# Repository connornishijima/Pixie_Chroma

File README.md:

<br>

**PIXIE CHROMA** is a dual-5x7 character display for Arduino, that can be easily chained to create easy-to-use displays as long or tall as you'd like! Featuring 70 addressable RGB LEDs, Pixie Chroma can be controlled with as little as a single GPIO! (***Make sure to [follow our Twitter](https://twitter.com/lixielabs) for official news!***)

---------------------------------------------------------------------------------
<p align="center">
  &nbsp;&nbsp;· · ·&nbsp;&nbsp;
  <a href="https://connornishijima.github.io/Pixie_Chroma/?section=getting-started"><b>GETTING STARTED</b></a>
  &nbsp;&nbsp;· · ·&nbsp;&nbsp;
  <a href="https://connornishijima.github.io/Pixie_Chroma/?section=docs"><b>LIBRARY DOCS</b></a>
  &nbsp;&nbsp;· · ·&nbsp;&nbsp;
  <a href="https://connornishijima.github.io/Pixie_Chroma/?section=datasheet"><b>DATASHEET</b></a>
  &nbsp;&nbsp;· · ·&nbsp;&nbsp;
  <a href="https://github.com/connornishijima/Pixie_Chroma/tree/main/extras/OSHW"><b>OSHW</b></a>
  &nbsp;&nbsp;· · ·&nbsp;&nbsp;
  <a href="https://connornishijima.github.io/Pixie_Chroma/?section=purchase"><b>PURCHASE</b></a>
  &nbsp;&nbsp;· · ·&nbsp;&nbsp;
</p>
<p align="center">

</p>

---------------------------------------------------------------------------------

# Pixie Chroma Is the Display We Always Wanted

**Pixie Chroma is a project that we here at Lixie Labs are incredibly passionate about!** In this third iteration, we have finally created the best RGB text display we've ever used. While we loved our original Pixie models, we felt that you couldn't get the same level of creativity that you **can** get with Pixie Chroma. With its ability to be dropped into any breadboard and coded with any experience level, these displays have a wide range of potential uses, meaning anybody in the maker community can find a use for them! Pixie Chroma is our gift to you.

# Two Big New Features

Along with full RGB control, and an absolute **UNIT** of an Arduino Library, we are introducing two other **big** new features with this release: **Quad Mode** and **Shortcodes**.

----------------------------------------------------------

**Quad mode is made specifically for those wishing to drive their displays faster.** By *optionally* sending the data in four parallel streams with Quad Mode, you can expect to see a ~3.75x increase in speed! For example, if you had 12 Pixie Chromas, you can wire four GPIO of your microcontroller to the 1st, 4th, 7th, and 10th Pixie. Each GPIO is now only responsible for the data of three Pixie Chromas compared to *only one GPIO feeding all 12*. With this, you can run animations, scrolling, and color palettes more smoothly or free up processor time!

**NOTE:** Quad Mode currently uses hard-coded GPIO pins depending on your microcontroller. To see which pins are needed, visit [the documentation for begin_quad()](https://connornishijima.github.io/Pixie_Chroma/docs/class_pixie_chroma.html#af4c7b1051ce21bf03cfd69d30869fa6c).

----------------------------------------------------------

Our next big feature is **Shortcodes**, a **super simple way to show icons beyond the alphanumeric ASCII set and easily create animations!** We have an extensive library of 230+ built-in icons that are accessible by name within *other* strings. See the example above. Whether you want global currency symbols, weather states, schematic symbols, diacritics (àãåâä), or various mathematical typography such as pi, we probably have you covered. And, if we don't, you can make your own with the magical Shortcode Editor.

## Shortcode Editor

Our favorite part of these icons is how easy it is to make your own! With [our online/offline editor](https://connornishijima.github.io/Pixie_Chroma/?section=shortcodes), you can create any shape or image (so long as it fits in a 5x7 grid) and the editor will directly show the code that would print that shape!

This is one of the most creative outlets for cool display enthusiasts, since you can easily make custom frame-by-frame animations of your own! We are currently working on a way to create looping animations directly within the editor, and are excited to show it when it is complete.

# A New Standard for Arduino Libraries

**We pride ourselves in how easy our products are to use.** We have kept the wiring very simple, with only three wires connected to each breadboard-friendly display. Our code also has many examples that are explained line-by-line so that anybody can understand them. We even include [template Arduino Sketches](https://github.com/connornishijima/Pixie_Chroma/blob/main/examples/04_Minimal_Sketches/01_Standard/01_Standard.ino) to skip the parts newcomers find tedious, like `#include` directives and class definitions. Many advanced projects that even seasoned coders would find challenging are hassle-free with the Pixie Chroma library!

```cpp
#include "Pixie_Chroma.h" // Include library
PixieChroma pix;
#define PIXIES_X  6  // Total amount and         x x x x x x
#define PIXIES_Y  2  // arrangement of Pixies =  x x x x x x

void setup() {
  pix.begin( 13, PIXIES_X, PIXIES_Y ); // ... Use Pin 13
  pix.color( CRGB::Blue ); // ............... Set color to blue
}

void loop() {
  pix.clear(); // ..................... Clear display
  pix.println( "Hello World!" ); // ... Write text on first row
  pix.print( millis() ); // ........... Write the value of millis() on the second row
  pix.show(); // ...................... Show changes
}
```
# Amazing Documentation  

[Pixie Chroma's documentation](https://connornishijima.github.io/Pixie_Chroma/?section=docs) is complete, accurate, and easy to understand. Each function in the library is fully documented and code examples are sprinkled liberally throughout.

# Supported Platforms

Pixie Chroma is a bit RAM heavy for its effects and color processing. 8 Pixie Chroma PCBs is 560 LEDs, so that's 1,680 bytes just for the color data! Add in the masking tricks, XY mapping and more, and you're unfortunately not going to get a set of Chromas working on an older microcontroller like the ATMega328p with only 2K of SRAM. ***However***, more modern controllers like those from Espressif are perfectly fine! (ESP8266 has 80KiB of RAM!)

The Pixie Chroma library also uses FastLED as a dependency, so FastLED itself also needs compatibility before we can support it here. *This is why the RP2040 is not yet supported. Soon!*

## Fully Supported Microcontrollers

- ESP8266 (Adafruit HUZZAH, Wemos D1 Mini, etc.)
- ESP32 / ESP32-S2 (TinyPico, HUZZAH32, TinyS2)
- Teensy 3.x (Possibly Teensy 4.x, not yet tested)

## Currently Planned Support

- RP2040 (Needs FastLED port)
- ~ESP32-S2 (Needs testing)~ *Confirmed working*
- ESP32-S3 (Needs testing)
- SAMD21 (TODO, has been hard to get)

If you have success running Pixie Chroma on a controller not currently in this list, let us know! We'd be happy to incorporate it. (You'll need to modify [Pixie_Chroma.h](https://github.com/connornishijima/Pixie_Chroma/blob/main/src/Pixie_Chroma.h) to accept the new compilation target first.)

# Dedication to Our Craft

Lixie Labs is a homegrown business **dedicated to furthering open source hardware and software** in both the hobbyist and professional electronics industry. To this day, we still receive emails from customers asking us how to get their hands on products we no longer produce. Luckily, anybody can still create their own Lixies or even earlier versions of Pixies without us because we've left the entire process open for others. We hope to see all of our projects outlive us!

**Pixie Chroma is OSHWA certified ([UID US002058](https://certification.oshwa.org/us002058.html))**, we've created an [extensive datasheet](https://connornishijima.github.io/Pixie_Chroma/?section=datasheet), and every single function within the library comes with [documentation](https://connornishijima.github.io/Pixie_Chroma/?section=docs).

# Features & Specifications

- Dual-5x7 RGB LED matrices
- 3.7 to 5.5 VDC supply
- Fast bitmap control
- 8-bit global dimming
- 27.5 mm x 16.5 mm matrix size (10.16 PPI)
- 30 mm x 24 mm package

# Comparison Table

|                                              | Pixie Chroma                | 5x5 RGB Matrix Breakout      | Dot Star 8x8 Grid            |
| -------------------------------------------- | --------------------------- | -----------------------------| ---------------------------- |
| **Manufacturer**                             | Lixie Labs                  | Pimoroni                     | Adafruit                     |
| **Size**                                     | 30 mm x 24 mm               | 19 mm x 29 mm                | 25 mm x 36 mm                |
| **LED Count**                                | Dual 5x7 displays, 70 total | Single 5x5 display, 25 total | Single 8x8 display, 64 total |
| **Pixels Per Inch**                          | 10.16 PPI                   | 7.25 PPI                     | 8 PPI                        |
| **Experience Level**                         | All Levels                  | Intermediate                 | Beginner                     |
| **Open Source**                              | HW + SW                     | SW only                      | HW + SW                      |
| **Documented Code Functions**                | Yes                         | No                           | Yes                          |
| **Datasheet**                                | Yes                         | No                           | No                           |
| **Quad Mode** **¹**                          | Yes                         | No  (no parallel output)     | No  (no parallel output)     |
| **Shortcodes** **²**                         | Yes  (239 included)         | N/A                          | N/A                          |
| **Breadboard Compatible**                    | Yes                         | No                           | No                           |
| **Power Management Features**                | Yes                         | No                           | No                           |
| **Easy Text Rendering**                      | Yes                         | No                           | No                           |
| **Non Blocking Animation**                   | Yes                         | No                           | No                           |
| **Predefined Color Palettes and Animations** | Yes                         | No                           | No                           |
| **Price Per LED**                            | $0.32                       | $0.49                        | $0.39                        |

**¹** _Quad Mode allows you to update your displays faster by using four GPIO at once!_  
**²** _Shortcodes like `[:HEART:]` let you use over 230 built-in icons by name and even create your own!_  

# Support & Documentation

**As you can see, Pixie Chroma is as easy or as advanced as you need.** Luckily, you don't need to dive into documentation to get started - the included examples (`File -> Examples -> Pixie_Chroma`) provide a template you can easily modify for your own projects.

For further information, you can check out the:

- [Getting Started Guide](https://connornishijima.github.io/Pixie_Chroma/?section=getting-started)
- [Shortcode Library](https://connornishijima.github.io/Pixie_Chroma/?section=shortcodes)
- [Arduino Library Documentation](https://connornishijima.github.io/Pixie_Chroma/?section=docs)
- [Datasheet](https://connornishijima.github.io/Pixie_Chroma/?section=datasheet)
- [Twitter](https://twitter.com/lixielabs) - We post quite often with Pixie Chroma updates and tricks!

Everything is open source and available. Our source code has been fully documented and all PCB designs and parts used are open and available:

- [GitHub](https://github.com/connornishijima/Pixie_Chroma/#readme)
- [OSHW](https://github.com/connornishijima/Pixie_Chroma/tree/main/extras/OSHW/#readme)
- [OHSWA certification](https://certification.oshwa.org/us002058.html)

# Sponsors

- **[Nitz](https://github.com/nitz)** 
- **[mlctrez](https://github.com/mlctrez)**

# Credits

**Developed by Connor Nishijima for Lixie Labs (2021)**

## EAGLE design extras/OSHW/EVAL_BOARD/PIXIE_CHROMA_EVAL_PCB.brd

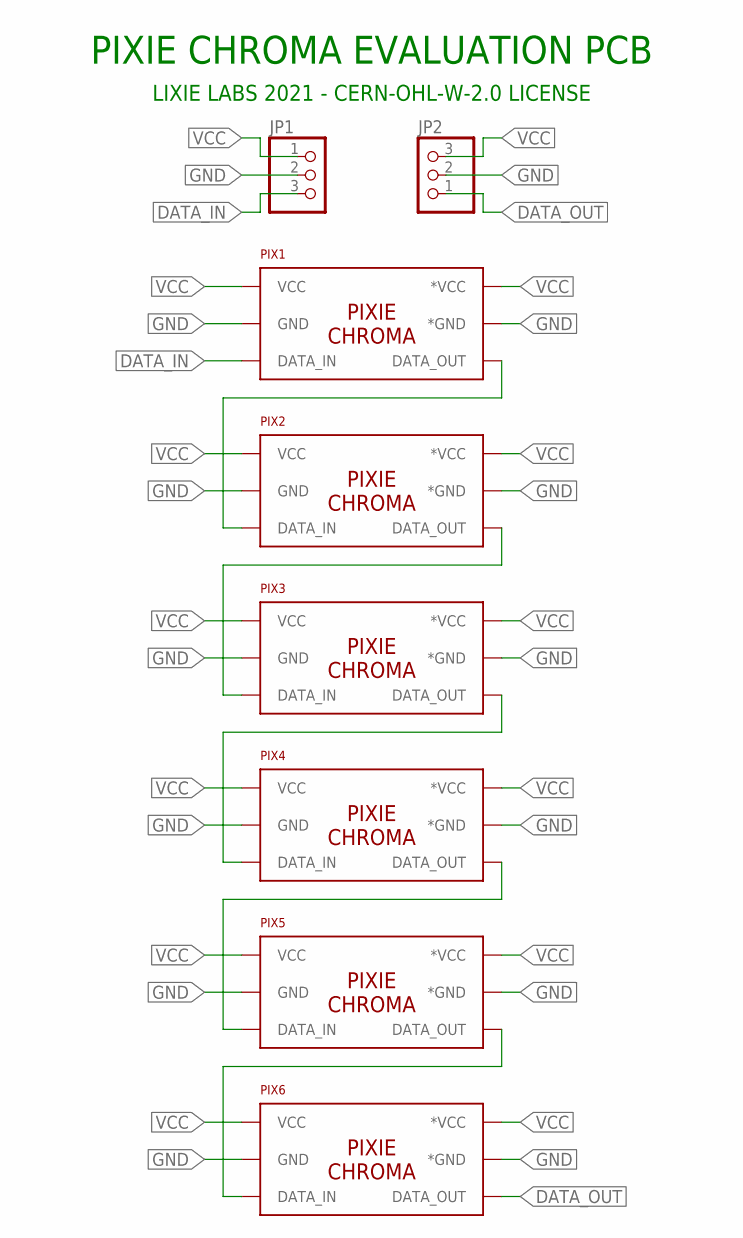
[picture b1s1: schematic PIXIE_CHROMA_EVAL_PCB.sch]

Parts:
JP1, JP2: PINHD-1X3; 1X03
PIX1, PIX2, PIX3, PIX4, PIX5, PIX6: CHROMA

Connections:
DATA_IN: JP1.3, PIX1.DATA_IN
DATA_OUT: JP2.1, PIX6.DATA_OUT
GND: JP1.2, JP2.2, PIX1.*GND, PIX1.GND, PIX2.*GND, PIX2.GND, PIX3.*GND, PIX3.GND, PIX4.*GND, PIX4.GND, PIX5.*GND, PIX5.GND, PIX6.*GND, PIX6.GND
unnamed: PIX1.DATA_OUT, PIX2.DATA_IN
unnamed: PIX2.DATA_OUT, PIX3.DATA_IN
unnamed: PIX3.DATA_OUT, PIX4.DATA_IN
unnamed: PIX4.DATA_OUT, PIX5.DATA_IN
unnamed: PIX5.DATA_OUT, PIX6.DATA_IN
VCC: JP1.1, JP2.3, PIX1.*VCC, PIX1.VCC, PIX2.*VCC, PIX2.VCC, PIX3.*VCC, PIX3.VCC, PIX4.*VCC, PIX4.VCC, PIX5.*VCC, PIX5.VCC, PIX6.*VCC, PIX6.VCC

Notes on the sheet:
PIXIE CHROMA EVALUATION PCB
LIXIE LABS 2021 - CERN-OHL-W-2.0 LICENSE

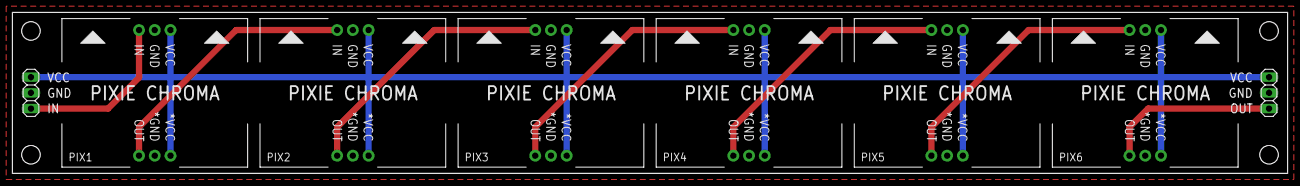
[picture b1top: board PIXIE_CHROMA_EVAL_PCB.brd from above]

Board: 2 copper layers, 206.0 x 26.0 mm, 8 parts (0 on the bottom side), 9 nets.

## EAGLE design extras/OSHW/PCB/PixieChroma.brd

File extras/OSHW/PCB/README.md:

# Pixie Chroma PCB Files

Here you can find our OSHW files for building your own Pixie Chroma!

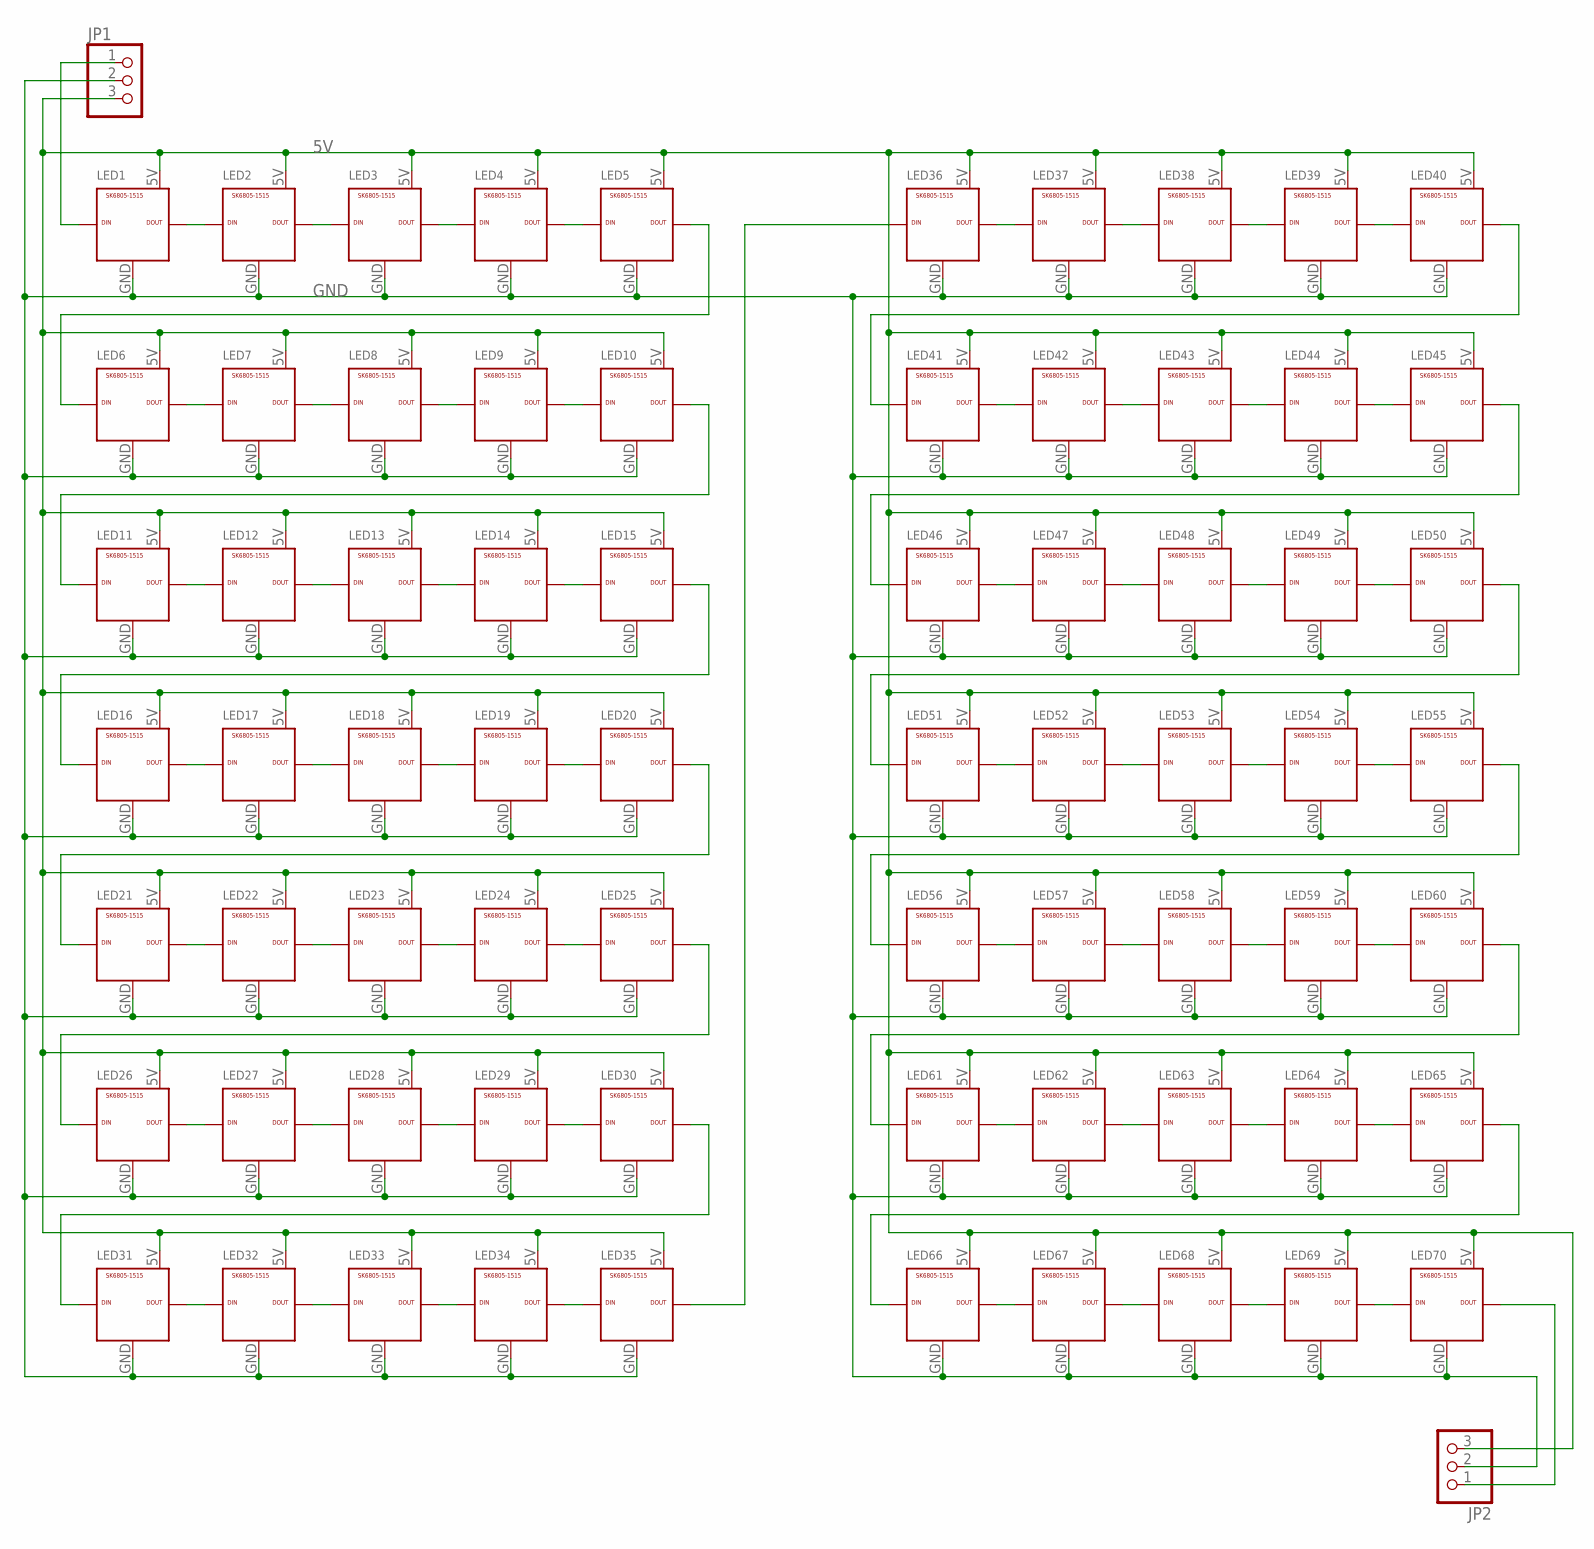
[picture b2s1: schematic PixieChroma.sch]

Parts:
JP1, JP2: PINHD-1X3; 1X03
LED1, LED2, LED3, LED4, LED5, LED6, LED7, LED8, LED9, LED10, LED11, LED12, LED13, LED14, LED15, LED16, LED17, LED18, LED19, LED20, LED21, LED22, LED23, LED24, LED25, LED26, LED27, LED28, LED29, LED30, LED31, LED32, LED33, LED34, LED35, LED36, LED37, LED38, LED39, LED40, LED41, LED42, LED43, LED44, LED45, LED46, LED47, LED48, LED49, LED50, LED51, LED52, LED53, LED54, LED55, LED56, LED57, LED58, LED59, LED60, LED61, LED62, LED63, LED64, LED65, LED66, LED67, LED68, LED69, LED70: SK6805-1515; 1515

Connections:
5V: JP1.3, JP2.3, LED1.5V, LED2.5V, LED3.5V, LED4.5V, LED5.5V, LED6.5V, LED7.5V, LED8.5V, LED9.5V, LED10.5V, LED11.5V, LED12.5V, LED13.5V, LED14.5V, LED15.5V, LED16.5V, LED17.5V, LED18.5V, LED19.5V, LED20.5V, LED21.5V, LED22.5V, LED23.5V, LED24.5V, LED25.5V, LED26.5V, LED27.5V, LED28.5V, LED29.5V, LED30.5V, LED31.5V, LED32.5V, LED33.5V, LED34.5V, LED35.5V, LED36.5V, LED37.5V, LED38.5V, LED39.5V, LED40.5V, LED41.5V, LED42.5V, LED43.5V, LED44.5V, LED45.5V, LED46.5V, LED47.5V, LED48.5V, LED49.5V, LED50.5V, LED51.5V, LED52.5V, LED53.5V, LED54.5V, LED55.5V, LED56.5V, LED57.5V, LED58.5V, LED59.5V, LED60.5V, LED61.5V, LED62.5V, LED63.5V, LED64.5V, LED65.5V, LED66.5V, LED67.5V, LED68.5V, LED69.5V, LED70.5V
DIN: JP1.1, LED1.DIN
DOUT: JP2.1, LED70.DOUT
GND: JP1.2, JP2.2, LED1.GND, LED2.GND, LED3.GND, LED4.GND, LED5.GND, LED6.GND, LED7.GND, LED8.GND, LED9.GND, LED10.GND, LED11.GND, LED12.GND, LED13.GND, LED14.GND, LED15.GND, LED16.GND, LED17.GND, LED18.GND, LED19.GND, LED20.GND, LED21.GND, LED22.GND, LED23.GND, LED24.GND, LED25.GND, LED26.GND, LED27.GND, LED28.GND, LED29.GND, LED30.GND, LED31.GND, LED32.GND, LED33.GND, LED34.GND, LED35.GND, LED36.GND, LED37.GND, LED38.GND, LED39.GND, LED40.GND, LED41.GND, LED42.GND, LED43.GND, LED44.GND, LED45.GND, LED46.GND, LED47.GND, LED48.GND, LED49.GND, LED50.GND, LED51.GND, LED52.GND, LED53.GND, LED54.GND, LED55.GND, LED56.GND, LED57.GND, LED58.GND, LED59.GND, LED60.GND, LED61.GND, LED62.GND, LED63.GND, LED64.GND, LED65.GND, LED66.GND, LED67.GND, LED68.GND, LED69.GND, LED70.GND
unnamed: LED3.DOUT, LED4.DIN
unnamed: LED2.DOUT, LED3.DIN
unnamed: LED1.DOUT, LED2.DIN
unnamed: LED4.DOUT, LED5.DIN
unnamed: LED18.DOUT, LED19.DIN
unnamed: LED8.DOUT, LED9.DIN
unnamed: LED7.DOUT, LED8.DIN
unnamed: LED6.DOUT, LED7.DIN
unnamed: LED9.DOUT, LED10.DIN
unnamed: LED13.DOUT, LED14.DIN
unnamed: LED5.DOUT, LED6.DIN
unnamed: LED17.DOUT, LED18.DIN
unnamed: LED12.DOUT, LED13.DIN
unnamed: LED11.DOUT, LED12.DIN
unnamed: LED14.DOUT, LED15.DIN
unnamed: LED10.DOUT, LED11.DIN
unnamed: LED16.DOUT, LED17.DIN
unnamed: LED19.DOUT, LED20.DIN
unnamed: LED15.DOUT, LED16.DIN
unnamed: LED23.DOUT, LED24.DIN
unnamed: LED22.DOUT, LED23.DIN
unnamed: LED21.DOUT, LED22.DIN
unnamed: LED24.DOUT, LED25.DIN
unnamed: LED20.DOUT, LED21.DIN
unnamed: LED28.DOUT, LED29.DIN
unnamed: LED27.DOUT, LED28.DIN
unnamed: LED26.DOUT, LED27.DIN
unnamed: LED29.DOUT, LED30.DIN
unnamed: LED25.DOUT, LED26.DIN
unnamed: LED33.DOUT, LED34.DIN
unnamed: LED32.DOUT, LED33.DIN
unnamed: LED31.DOUT, LED32.DIN
unnamed: LED34.DOUT, LED35.DIN
unnamed: LED30.DOUT, LED31.DIN
unnamed: LED38.DOUT, LED39.DIN
unnamed: LED37.DOUT, LED38.DIN
unnamed: LED36.DOUT, LED37.DIN
unnamed: LED39.DOUT, LED40.DIN
unnamed: LED35.DOUT, LED36.DIN
unnamed: LED43.DOUT, LED44.DIN
unnamed: LED42.DOUT, LED43.DIN
unnamed: LED41.DOUT, LED42.DIN
unnamed: LED44.DOUT, LED45.DIN
unnamed: LED40.DOUT, LED41.DIN
unnamed: LED48.DOUT, LED49.DIN
unnamed: LED47.DOUT, LED48.DIN
unnamed: LED46.DOUT, LED47.DIN
unnamed: LED49.DOUT, LED50.DIN
unnamed: LED45.DOUT, LED46.DIN
unnamed: LED53.DOUT, LED54.DIN
unnamed: LED52.DOUT, LED53.DIN
unnamed: LED51.DOUT, LED52.DIN
unnamed: LED54.DOUT, LED55.DIN
unnamed: LED50.DOUT, LED51.DIN
unnamed: LED58.DOUT, LED59.DIN
unnamed: LED57.DOUT, LED58.DIN
unnamed: LED56.DOUT, LED57.DIN
unnamed: LED59.DOUT, LED60.DIN
unnamed: LED55.DOUT, LED56.DIN
unnamed: LED63.DOUT, LED64.DIN
unnamed: LED62.DOUT, LED63.DIN
unnamed: LED61.DOUT, LED62.DIN
unnamed: LED64.DOUT, LED65.DIN
unnamed: LED60.DOUT, LED61.DIN
unnamed: LED68.DOUT, LED69.DIN
unnamed: LED67.DOUT, LED68.DIN
unnamed: LED66.DOUT, LED67.DIN
unnamed: LED69.DOUT, LED70.DIN
unnamed: LED65.DOUT, LED66.DIN

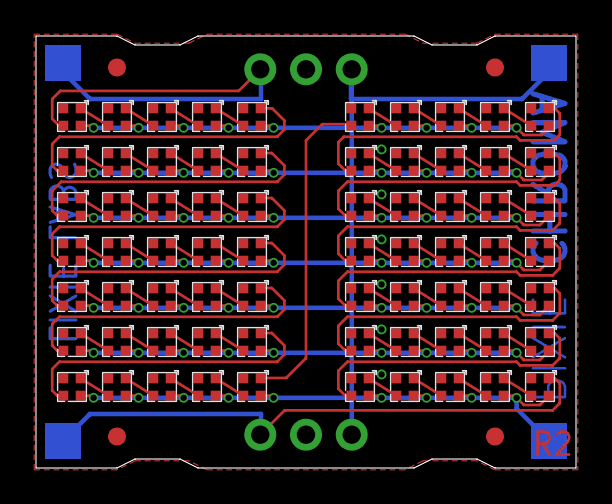
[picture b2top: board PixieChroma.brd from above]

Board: 2 copper layers, 30.0 x 24.0 mm, 76 parts (0 on the bottom side), 73 nets.

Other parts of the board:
U$1, U$2, U$3, U$4: CIRCLE-1MM-2R

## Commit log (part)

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2021-11-14 Auto commit.
2021-11-15 Added animation example
2021-11-15 Added power budgeting example
2021-11-15 Added gamma correction example
2021-11-15 Formatting fixes
2021-11-15 Added update modes example
2021-11-15 Added XY/UV example
2021-11-15 Renamed ANIMATION_PALETTE_SHIFT to _PALETTE_SHIFT
2021-11-16 [ImgBot] Optimize images
    *Total -- 8,593.46kb -> 8,582.43kb (0.13%)
    /docs/search/mag_sel.svg -- 2.32kb -> 0.72kb (68.88%)
    /docs/search/close.svg -- 1.25kb -> 0.73kb (42.13%)
    /extras/OSHW/oshw_facts.svg -- 8.83kb -> 7.54kb (14.55%)
    /extras/img/apple_icon.png -- 35.35kb -> 34.32kb (2.9%)
    /docs/doc.png -- 0.73kb -> 0.72kb (0.94%)
2021-12-03 Added Teensy 3.x Support!
2021-12-03 Automated Cleanup
2021-12-03 Fixed Teensy pin mappings
2021-12-03 Documented mask shift functions
2021-12-03 Added public class variables to keywords.txt
2021-12-03 Renamed NUM_LEDS to led_count for consistency
2021-12-03 Library example restructuring
2021-12-03 Added text justification functions
2021-12-03 Added print_color() functionality
2021-12-03 Moved docs directory to extras
2021-12-03 Moved docs
2021-12-03 Fixed set_palette behavior with custom print colors
2021-12-04 Added one-line scrolling functionality
2021-12-04 Shortcodes now work in lowercase too
2021-12-04 Added Serial Monitor example
2021-12-04 Update logo
2021-12-04 Clarified set_frame_rate_target()
2021-12-04 [ImgBot] Optimize images
    *Total -- 882.68kb -> 855.87kb (3.04%)
    /docs/search/mag_sel.svg -- 2.32kb -> 0.72kb (68.88%)
    /docs/search/close.svg -- 1.25kb -> 0.73kb (42.13%)
    /extras/img/logo.png -- 863.35kb -> 838.81kb (2.84%)
    /docs/doc.png -- 0.73kb -> 0.72kb (0.94%)
    /docs/doxygen.svg -- 15.02kb -> 14.90kb (0.83%)
2021-12-14 Added Custom Shortcode support!
2021-12-14 Added automatic icon recognition! :)
2021-12-14 Removed selection capability on Pixie preview
2021-12-15 Grouped and alphabetized public functions!
2021-12-28 Added EAGLE OSHW library files!
2021-12-28 Updated EAGLE library and eval PCB with better pads
2021-12-28 Labeled schematic with license info
2021-12-28 Added STL Model
2021-12-28 Added README images
2021-12-28 Added introduction images
2021-12-28 [ImgBot] Optimize images
    *Total -- 8,536.51kb -> 8,150.38kb (4.52%)
    /docs/search/mag_sel.svg -- 2.32kb -> 0.72kb (68.88%)
    /docs/search/close.svg -- 1.25kb -> 0.73kb (42.13%)
    /extras/img/rm2.jpg -- 47.33kb -> 42.68kb (9.83%)
    /extras/img/rm6.jpg -- 3,124.79kb -> 2,926.29kb (6.35%)
    /extras/img/rm1.png -- 5,337.54kb -> 5,156.82kb (3.39%)
2021-12-28 Clarified begin_quad()
2021-12-28 Fixed naming
2022-03-28 Added final Shortcodes example code
2022-04-07 Added vendor interstitial page to Purchase link
2022-04-07 Added purchase page
2022-04-07 Fixed margins
2022-04-07 Added note about supported platforms, thanks @ladyada!
2022-04-07 Added purchase link to README header
2022-04-07 Clarified supported platforms in compile error message
2022-04-07 Added Quad Mode pins clarification
2022-04-07 [ImgBot] Optimize images
    *Total -- 12,192.50kb -> 11,758.54kb (3.56%)
    /docs/search/mag_sel.svg -- 2.32kb -> 0.72kb (68.88%)
    /docs/search/close.svg -- 1.25kb -> 0.73kb (42.13%)
    /extras/img/cs_logo.svg -- 2.65kb -> 2.32kb (12.41%)
    /extras/img/rm2.jpg -- 47.33kb -> 42.68kb (9.83%)
    /extras/img/rm3.jpg -- 42.50kb -> 39.23kb (7.68%)
2022-04-07 Added Adafruit demo GIF
2022-04-07 Added GIF demo
2022-04-07 Forced recompile with GitHub Actions
2022-04-07 Forced recompilation using GitHub Actions
2022-04-14 Further work on links and Step 7
2022-04-14 Added ToC links
2022-04-14 Glossary reformat
2022-04-14 Updated log
2022-04-14 Added first beginner function docs
2022-04-14 Manual doc rendering trigger
2022-04-14 Manual retrigger
2022-04-14 Added Getting Started link
2022-04-14 Swapped arduino IDE photo
2022-04-14 Added Arduino Library images
2022-04-14 Added serial port photos
2022-04-14 [ImgBot] Optimize images
    *Total -- 19,856.99kb -> 19,161.27kb (3.5%)
    /docs/search/mag_sel.svg -- 2.32kb -> 0.72kb (68.88%)
    /extras/img/ports_connected.png -- 34.40kb -> 19.74kb (42.62%)
    /extras/img/ports_empty.png -- 32.07kb -> 18.49kb (42.34%)
    /docs/search/close.svg -- 1.25kb -> 0.73kb (42.13%)
    /extras/img/arduino_example_location.png -- 106.06kb -> 64.62kb (39.08%)
2022-04-15 Added wiring images
2022-04-15 Updated tutorial images
2022-04-15 Added gold arrow indicator
2022-04-15 fixed wiring line
2022-04-15 Removed "under construction" message
2022-04-15 Fixed top margin
2022-04-15 Added breadboard diagram
2022-04-15 Added auto note highlighting
2022-04-15 Rearranged ToC location
2022-04-15 [ImgBot] Optimize images
    *Total -- 2,531.12kb -> 2,285.57kb (9.7%)
    /extras/img/wiring3.jpg -- 430.86kb -> 374.74kb (13.03%)
    /extras/img/wiring4.jpg -- 446.69kb -> 389.05kb (12.9%)
    /extras/img/wiring1.jpg -- 505.54kb -> 462.46kb (8.52%)
    /extras/img/wiring5.jpg -- 481.24kb -> 441.17kb (8.33%)
    /extras/img/wiring2.jpg -- 620.22kb -> 574.24kb (7.41%)
2022-04-15 Added FastLED.delay() passthrough
2022-04-15 Renamed conflicting delay() function
2022-04-15 Reverted delay name change
2022-04-16 Forced markdown parser to not violate CORS policy
    Thanks @ladyada, good catch.
2022-04-19 Patch for GitHub CVE-2022-24765
2022-04-19 Auto commit
2022-04-19 Create getting_started.md
    Replaced after CI killed it :(
2022-04-19 Create getting_started.html
    Replaced after CI killed it :(
2022-04-19 Fixed rm -r *tar* string to not kill the "getting sTARted" guide.
2022-04-19 Restored Getting Started guide after CI killed it
2022-04-19 Manual retrigger of CI
2022-04-19 Manual CI retrigger
2022-04-19 Possible favicon fix
2022-04-19 Documentation expansion/terminology corrections for basic functions
2022-04-19 Added Shortcodes to Getting Started guide
2022-04-19 Added Color Animation docs to Getting Started, renamed set_color_animation()
2022-04-19 Fixed color animation function naming
2022-04-19 Function naming fix
2022-04-19 Added extra Getting Started Guide link
2022-04-19 set_color_animation() rename now defined
2022-04-21 Added "view directly" button to docs site for ease of printing
2022-04-21 Webhook testing
2022-04-21 Removed webhook test change
2022-04-21 Slightly darkened "view directly" text
2022-04-23 Fixed header sizing
2022-04-23 Fixed OSHW link for off-site rendering
2022-04-23 Potential formatting fix
2022-04-23 Added "about" landing page
2022-04-23 Image size reduction and formatting
2022-04-23 Removed old imagery
2022-04-23 Images fix and datasheet trimming
2022-04-23 Added video preview
2022-04-23 Removed banner in favor of video thumbnail
2022-04-23 Transparency fix
2022-04-23 Slightly brightened
2022-04-23 Slightly darkened
2022-04-23 Fixed non-HTML compliant symbols and Quad Mode link
2022-04-23 Added SK6805-EC15 datasheet link
2022-04-23 Corrected datasheet logo
2022-04-23 Rearranged header
2022-04-23 Styled separators
2022-04-23 Improved header formatting
2022-04-23 CSS fix
2022-04-23 Better menu border
2022-04-23 Forced CI rebuild
2022-04-24 [ImgBot] Optimize images
    *Total -- 5,084.40kb -> 4,737.22kb (6.83%)
    /docs/search/mag_sel.svg -- 2.32kb -> 0.72kb (68.88%)
    /docs/search/close.svg -- 1.25kb -> 0.73kb (42.13%)
    /extras/img/rm5.jpg -- 287.36kb -> 240.83kb (16.19%)
    /extras/img/rm4.jpg -- 265.08kb -> 226.88kb (14.41%)
    /extras/img/wiring3.jpg -- 193.85kb -> 174.88kb (9.78%)
2022-04-25 Added Twitter follower count tracking project
2022-04-25 Potential CI fix
2022-04-27 Open char_buf length issue
2022-06-23 Added note about minimum IDE version support
2022-06-23 Added Tindie vendor link
2022-08-07 Added Mouser as a vendor! :mouse:
2022-09-22 test with ESP32-S2 and ESP32-S3 targets
2022-09-22 run tests with ESP32-S2 and ESP32-S3 targets
2022-09-23 don't use FastLED's I2S mode on the ESP32-S2 and ESP32-S3
    set up acceptable pin definitions for ESP32-S2 and ESP32-S3 (compatible with FastLED 3.5.0)
    change quad mode pin for ESP32-S2 and ESP32-S3 from 27 to 26 as 27 is not usable
2022-09-23 Added initialization value to x_offset_chars
2022-09-23 Removed unused variables
2022-09-24 fix CI warnings as errors issue
    properly configure FastLED for ESP32-S3

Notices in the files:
parts and their libraries:
PixieChroma: (c) 2021 - CERN-OHL-W-2.0 LICENSE
